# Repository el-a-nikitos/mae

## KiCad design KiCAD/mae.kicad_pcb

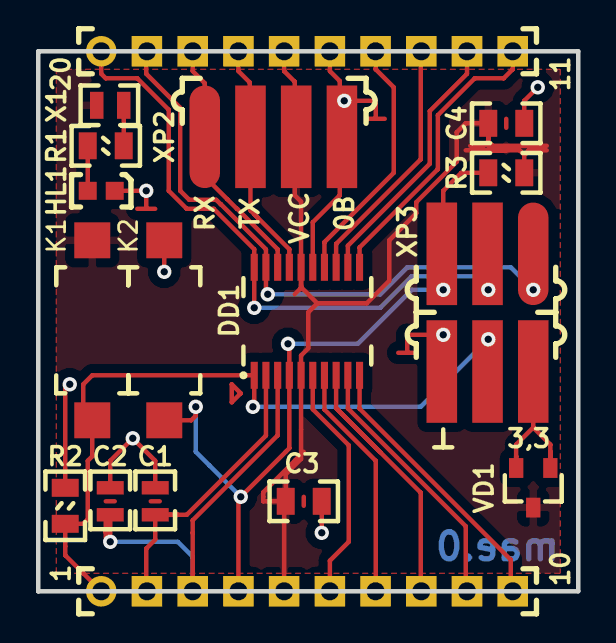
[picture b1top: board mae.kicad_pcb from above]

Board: 2 copper layers, 30.0 x 30.0 mm, 17 parts (0 on the bottom side), 22 nets.

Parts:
C1, C2: 12Ф, 0603; Конденсатор_SMD_0603
C3, C4: 4.7мкФ, 0805; Конденсатор_SMD_0805
DD1: STM32F030F4P6(TSSOP-20); SSOP-20
HL1: Светодиод; Светодиод_SMD_0603
K1, K2: 1437566-3 (FSMSM); Кнопка_FSMSM
R1: Резистор_0,125Вт; Резистор_SMD_0805_0,125Вт
R2, R3: 20к, 0805; Резистор_SMD_0805_0,125Вт
VD1: Диод_шоттки(2-анод); Диод_BAR43CFILM_SOT-23
X1: перемычка_разрывная; Конденсатор_SMD_0603
XP1, XP4: Вилка_PLS10; Вилка_PLS10_вертикальная
XP2: Вилка_PLS4; Вилка_PLS4_угловая_вертикальная
XP3: Вилка_PLD6_ПРОГ; Вилка_PLD6_угловая_вертикальная

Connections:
/0В: C1.2, C2.2, C3.2, C4.2, DD1.15, HL1.2, K2.2, R2.1, XP2.4, XP3.6, XP4.6
/ADC5_6V: DD1.14, XP4.7
/ADCT2: DD1.11, XP4.10
/ADC_3V: DD1.13, XP4.8
/ADC_T1: DD1.12, XP4.9
/BOOT_mode: DD1.1, K1.1, R2.2, XP1.1, XP3.4
/CLK: DD1.20, XP3.3, XP4.1
/DIO: DD1.19, XP3.1, XP4.2
/EnRS: DD1.10, XP1.10
/G1: DD1.7, XP1.7
/G2: DD1.6, XP1.6
/G3: C2.1, DD1.3, XP1.3
/G4: C1.1, DD1.2, XP1.2
/RES: DD1.4, K2.1, R3.2, XP1.4, XP3.5
/RX: DD1.9, XP1.9
/RXboot_SDA: DD1.18, XP2.1, XP4.3
/TX: DD1.8, XP1.8
/TXboot_SCL: DD1.17, XP2.2, XP4.4
/VCC: C3.1, C4.1, DD1.5, DD1.16, K1.2, R3.1, VD1.2, X1.2, XP1.5, XP2.3, XP4.5
/VCCprog: VD1.1, XP3.2
unnamed: HL1.1, R1.2
unnamed: R1.1, X1.1

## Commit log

2019-02-26 проект 30х30, полуотверстия
2019-02-27 добавлена шелкография сзади, переделана нумерация как ssop20
2019-02-28 добавлены герберы, на меди добавлены метки ключей
2019-03-09 сгенерирован ПриветМир проект
2019-03-10 переконфигурирован ПриветМир на физическое мигание светодиодом
